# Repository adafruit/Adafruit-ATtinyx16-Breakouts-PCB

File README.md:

## Adafruit ATtinyx16 Breakouts with seesaw - STEMMA QT / Qwiic PCB

<a href="http://www.adafruit.com/products/5681"><br/>
Click here to purchase one from the Adafruit shop</a>
<a href="http://www.adafruit.com/products/5690"><br/>
Click here to purchase one from the Adafruit shop</a>

PCB files for the Adafruit ATtiny816 and ATtiny1616 Breakouts with seesaw - STEMMA QT / Qwiic. 

Format is EagleCAD schematic and board layout
* https://www.adafruit.com/product/5681
* https://www.adafruit.com/product/5690

### Description

These breakout boards are a "three in one" product:

* The ATtinyx16 are part of the 'next gen' of AVR microcontrollers, and now we have cute development/breakout boards for them, with just enough hardware to get the chip up and running.
* It's also an Adafruit seesaw board. Adafruit seesaw is a near-universal converter framework which allows you to add and extend hardware support to any I2C-capable microcontroller or microcomputer. Instead of getting separate I2C GPIO expanders, ADCs, PWM drivers, etc, seesaw can be configured to give a wide range of capabilities.
* Finally, with STEMMA QT connectors on it, you could use it as either an I2C controller or peripheral with plug-and play support.

We primarily designed this board for our own use: it's a mini dev board that lets us design with the ATtiny816 just like we did for the ATSAMD09. With the 2021-2022 silicon shortage, we're adapting some of our SAMD09 designs to the ATTiny8xx series and wanted a quick minimal board to test code on.

Each breakout comes with the assembled and tested board, as well as some header strips. Each PCB is fairly minimal and contains:

The ATtiny816 and ATtiny1616 are identical in specifications except for storage space: 
* The ATtiny816 has 8KB flash, 512 bytes of RAM, 128 bytes of EEPROM
* The ATtiny1616 has 16KB flash, 2KB of RAM, 256 bytes of EEPROM

* Internal oscillator can run up to 20MHz
* Internal hardware multiplier
* Can run from 2V to 5V power/logic (check the datasheet for max speed at desired power)
* 3.3V regulator - by default we run at the Vin voltage, which can be 5V, but there's a solder jumper on the bottom if you'd like to select 3V logic.
* Green power LED
* Red indicator LED
* Two STEMMA QT I2C connectors with 10K pullup resistors, connected to pins 8 and 9

These boards comes pre-programmed with seesaw peripheral code that will let it act as an "I2C to something" converter, basically a little I2C-controlled friend to do all the timing-sensitive things many microcontrollers and microcomputers are not good at.

For example, using these breakouts with the pre-burned seesaw firmware gives you

* 12 x GPIO with selectable pullup resistors: 0-5, 6, 8, 11, 14, 15, 16
* 9 x 10-bit ADC inputs - pins 0, 1, 2, 3, 4, 5, 14, 15, 16
* 5 x 8-bit PWM outputs - pins 0, 1, 7, 11, 16
* 1 x NeoPixel output (up to 60 pixels)
* 1 x EEPROM with 127 byte of NVM memory (handy for storing small access tokens or MAC addresses) - last byte of EEPROM is used for I2C address selection
* 1 x Interrupt output that can be triggered by any of the accessories - pin 6
* 2 x I2C address selection pins - pins 12 and 13
* 1 x Activity LED on pin 10, tied active low

Of course, you can configure or reprogram the chip to however you want to use it - we like using SpenceKonde's megaTinyCore which brings Arduino peripheral support to this series of chips. To program the chip you will need a 'UPDI' programmer, which you can make with a USB-to-Serial cable and a single 4.7K or 10K resistor.

Please note: The boards do not come with a bootloader. If you want to do development on seesaw (e.g. changing the configuration) you need a separate UPDI programming setup! The firmware we put on is available as this example sketch, compiled using the megaTinyCore. We don't provide any support for custom builds of seesaw - we think this is cool and useful for the Maker community!

For more details including the documentation on how to use seesaw, libraries for Arduino/CircuitPython/Raspberry Pi Python, schematics, and more check out the Adafruit seesaw guide

### License

Adafruit invests time and resources providing this open source design, please support Adafruit and open-source hardware by purchasing products from [Adafruit](https://www.adafruit.com)!

Designed by Limor Fried/Ladyada for Adafruit Industries.

Creative Commons Attribution/Share-Alike, all text above must be included in any redistribution. 
See license.txt for additional details.

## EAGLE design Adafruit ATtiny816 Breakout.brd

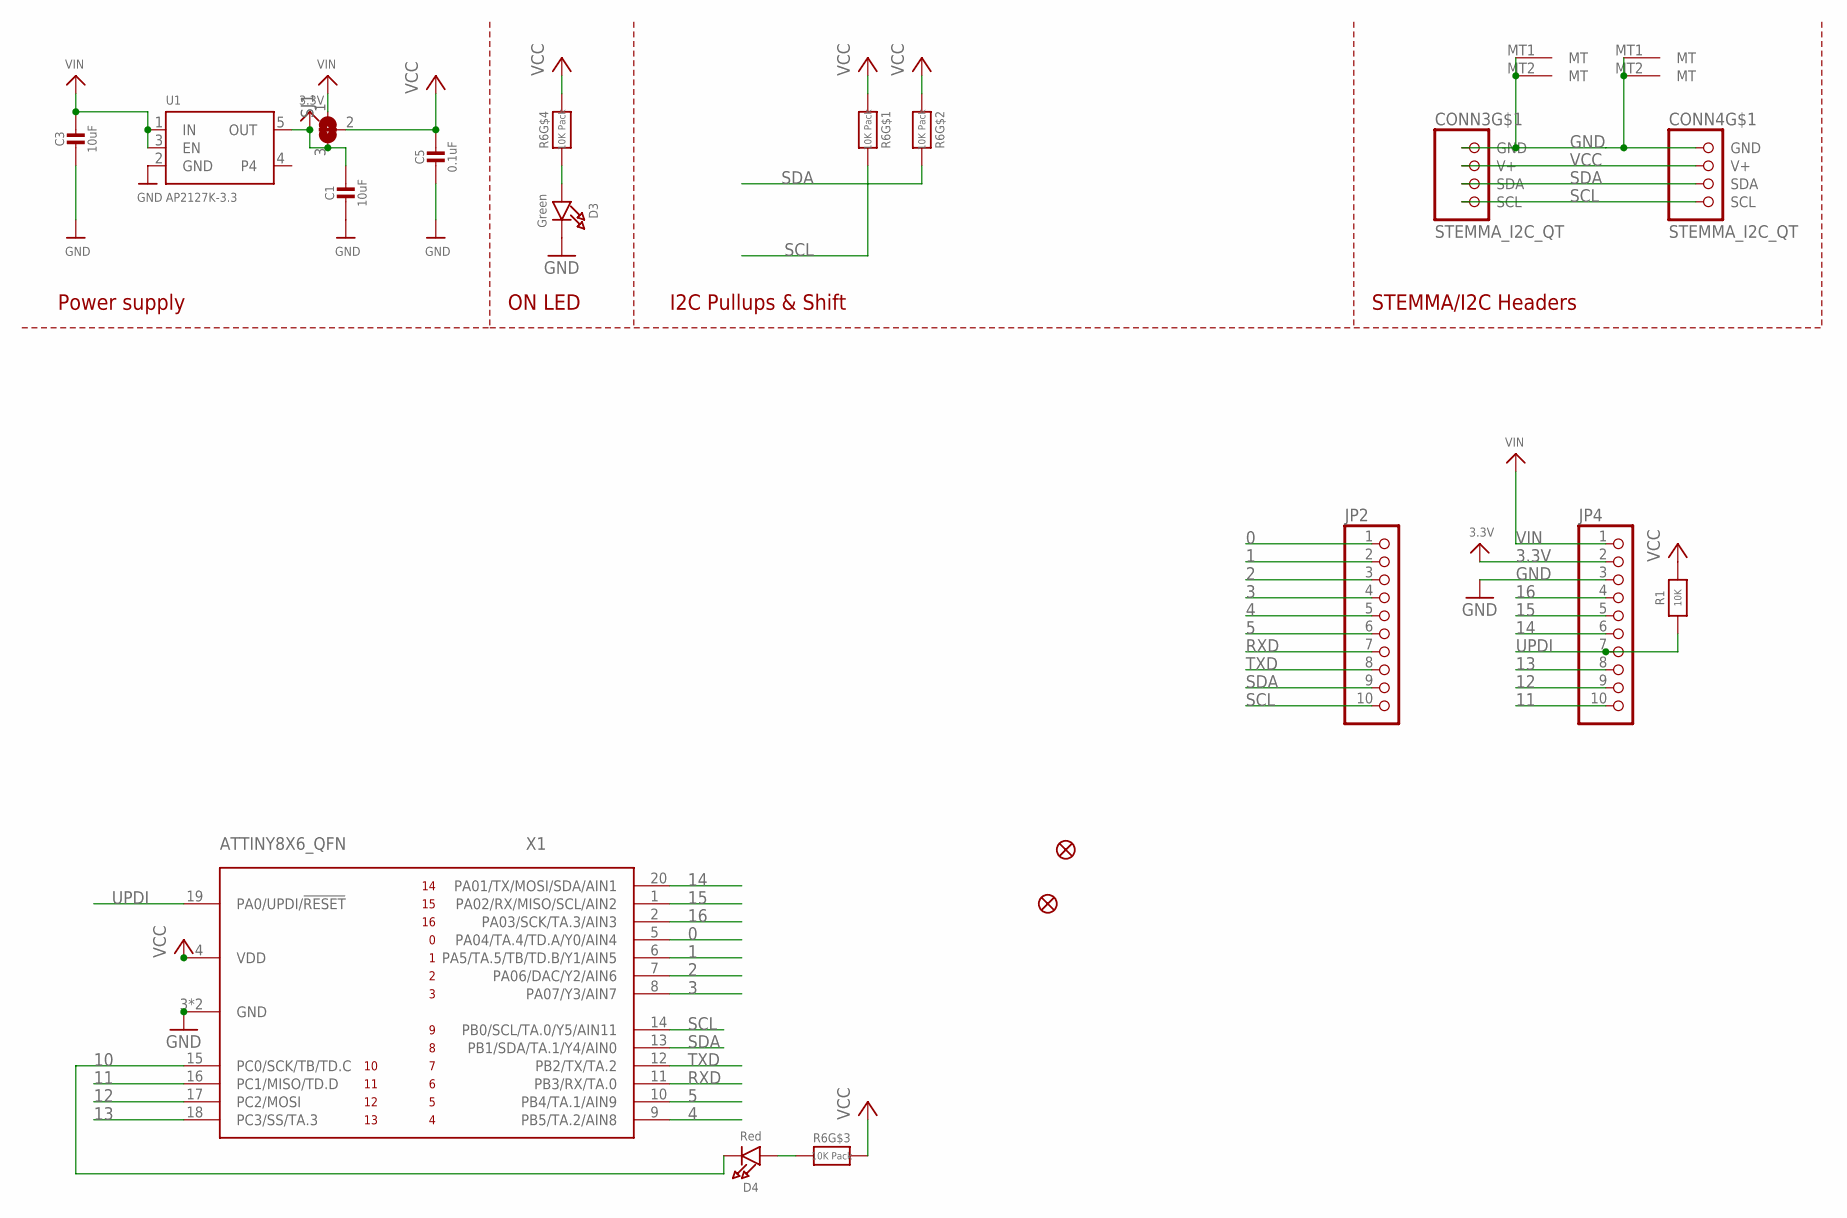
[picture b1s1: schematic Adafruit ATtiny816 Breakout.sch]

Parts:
C1: 10uF; 0805_10MGAP
C3: 10uF; 0805-NO
C5: 0.1uF; 0603-NO
CONN3, CONN4: STEMMA_I2C_QT; JST_SH4
D3: Green; CHIPLED_0603_NOOUTLINE
D4: Red; CHIPLED_0603_NOOUTLINE
FID1, FID2: FIDUCIAL_1MM
JP2, JP4: HEADER-1X1070MIL; 1X10_ROUND70
R1: 10K; 0603-NO
R6: 10K Pack; RESPACK_4X0603
SJ1: SOLDERJUMPER_2WAY; SOLDERJUMPER_2WAY_OPEN_NOPASTE
U1: AP2127K-3.3; SOT23-5
X1: ATTINY8X6_QFN; QFN20_3MM

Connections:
0: JP2.1, X1.5 (PA04/TA.4/TD.A/Y0/AIN4)
1: JP2.2, X1.6 (PA5/TA.5/TB/TD.B/Y1/AIN5)
2: JP2.3, X1.7 (PA06/DAC/Y2/AIN6)
3: JP2.4, X1.8 (PA07/Y3/AIN7)
3.3V: C1.1, JP4.2, SJ1.3, U1.5 (OUT)
4: JP2.5, X1.9 (PB5/TA.2/AIN8)
5: JP2.6, X1.10 (PB4/TA.1/AIN9)
10: D4.C, X1.15 (PC0/SCK/TB/TD.C)
11: JP4.10, X1.16 (PC1/MISO/TD.D)
12: JP4.9, X1.17 (PC2/MOSI)
13: JP4.8, X1.18 (PC3/SS/TA.3)
14: JP4.6, X1.20 (PA01/TX/MOSI/SDA/AIN1)
15: JP4.5, X1.1 (PA02/RX/MISO/SCL/AIN2)
16: JP4.4, X1.2 (PA03/SCK/TA.3/AIN3)
GND: C1.2, C3.2, C5.2, CONN3.1 (GND), CONN3.MT1 (MT), CONN3.MT2 (MT), CONN4.1 (GND), CONN4.MT1 (MT), CONN4.MT2 (MT), D3.C, JP4.3, U1.2 (GND), X1.3 (GND), X1.PAD (GND)
unnamed: D3.A, R6.4 (1)
unnamed: D4.A, R6.3 (1)
RXD: JP2.7, X1.11 (PB3/RX/TA.0)
SCL: CONN3.4 (SCL), CONN4.4 (SCL), JP2.10, R6.8 (2), X1.14 (PB0/SCL/TA.0/Y5/AIN11)
SDA: CONN3.3 (SDA), CONN4.3 (SDA), JP2.9, R6.7 (2), X1.13 (PB1/SDA/TA.1/Y4/AIN0)
TXD: JP2.8, X1.12 (PB2/TX/TA.2)
UPDI: JP4.7, R1.1, X1.19 (PA0/UPDI/!RESET)
VCC: C5.1, CONN3.2 (V+), CONN4.2 (V+), R1.2, R6.1, R6.2 (1), R6.5 (2), R6.6 (2), SJ1.2, X1.4 (VDD)
VIN: C3.1, JP4.1, SJ1.1, U1.1 (IN), U1.3 (EN)

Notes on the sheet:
I2C Pullups & Shift
STEMMA/I2C Headers
ON LED
Power supply

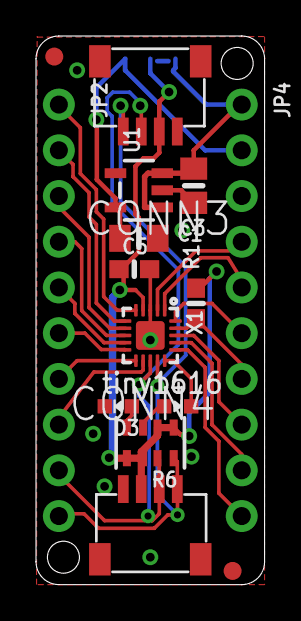
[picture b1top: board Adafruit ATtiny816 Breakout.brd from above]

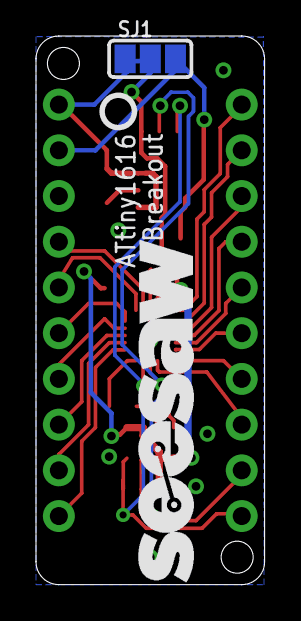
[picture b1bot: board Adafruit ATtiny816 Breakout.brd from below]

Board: 2 copper layers, 12.7 x 30.5 mm, 75 parts (27 on the bottom side), 24 nets.

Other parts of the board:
PLABEL0: PLABEL0
PLABEL1: PLABEL1
PLABEL2: PLABEL2
PLABEL3: PLABEL3
PLABEL4: PLABEL4
PLABEL5: PLABEL5
PLABEL6: PLABEL6
PLABEL7: PLABEL7
PLABEL8: PLABEL8
PLABEL9: PLABEL9
PLABEL10: PLABEL10
PLABEL11: PLABEL11
PLABEL12: PLABEL12
PLABEL13: PLABEL13
PLABEL14: PLABEL14
PLABEL15: PLABEL15
PLABEL17: PLABEL17
PLABEL18: PLABEL18
PLABEL19: PLABEL19
PLABEL20: PLABEL20
PLABEL21: PLABEL21
PLABEL22: PLABEL22
PLABEL23: PLABEL23
PLABEL24: PLABEL24
PLABEL25: PLABEL25
PLABEL26: PLABEL26
PLABEL27: PLABEL27
PLABEL28: PLABEL28
PLABEL29: PLABEL29
PLABEL30: PLABEL30
PLABEL31: PLABEL31
PLABEL32: PLABEL32
PLABEL33: PLABEL33
PLABEL35: PLABEL35
PLABEL36: PLABEL36
PLABEL37: PLABEL37
PLABEL38: PLABEL38
PLABEL39: PLABEL39
PLABEL40: PLABEL40
PLABEL41: PLABEL41
PLABEL42: PLABEL42
PLABEL43: PLABEL43
PLABEL44: PLABEL44
PLABEL45: PLABEL45
PLABEL46: PLABEL46
PLABEL47: PLABEL47
PLABEL48: PLABEL48
PLABEL49: PLABEL49
PLABEL50: PLABEL50
PLABEL51: PLABEL51
PLABEL52: PLABEL52
PLABEL53: PLABEL53
PLABEL54: PLABEL54
PLABEL55: PLABEL55
PLABEL56: PLABEL56
PLABEL57: PLABEL57
PLABEL58: PLABEL58
U$7: SEESAW_LOGO
U$12: PCBFEAT-REV-040

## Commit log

2023-02-23 cookiecutter output
2023-02-23 updating readme
2023-02-23 updating 816 image
2023-02-23 add link for 1616

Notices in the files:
parts and their libraries:
microbuilder: This work is placed in the public domain, and may be freely used for commercial and non-commercial work with the following conditions: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
